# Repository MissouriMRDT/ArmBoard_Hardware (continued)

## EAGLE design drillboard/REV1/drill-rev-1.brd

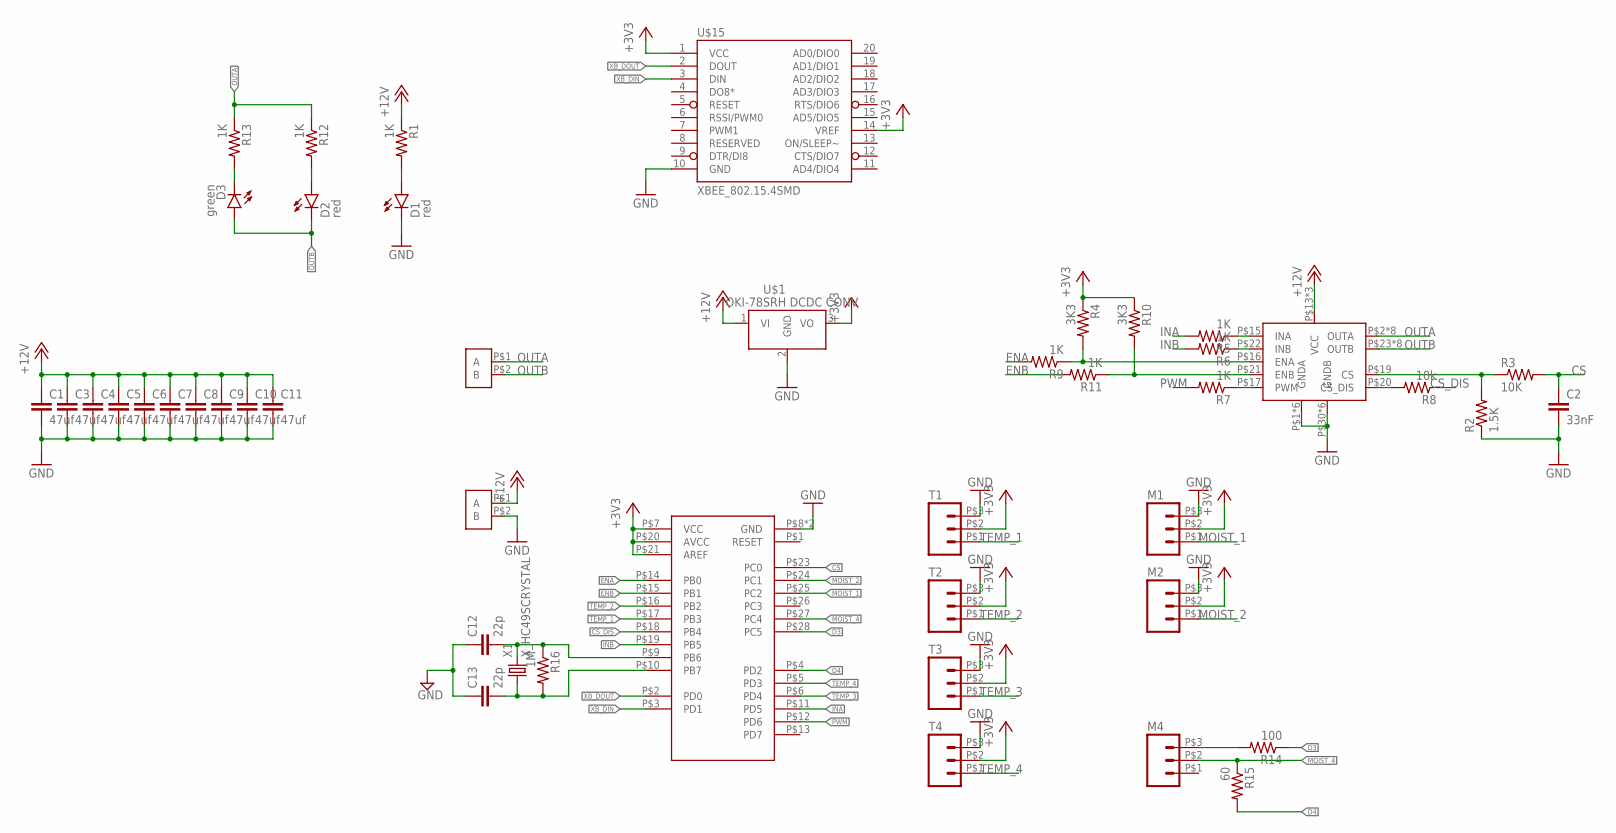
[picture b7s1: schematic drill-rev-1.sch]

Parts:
C1, C3, C4, C5, C6, C7, C8, C9, C10, C11: 47uf; 1210
C2: 33nF; 0603-CAP
C12, C13: 22p; 0603-CAP
D1, D2: red; LED-0603
D3: green; LED-0603
M1, M2, M4: M03VERT; MOLEX0436500328
R1, R5, R6, R7, R9, R11, R12, R13: 1K; 0603-RES
R2: 1.5K; 0603-RES
R3: 10K; 0603-RES
R4, R10: 3K3; 0603-RES
R8: 10k; 0603-RES
R14: 100; 1206
R15: 60; 1206
R16: 1M; 0603-RES
T1, T2, T3, T4: M03VERT; MOLEX0436500328
U$1: Q_OKI-78SR; OKI-78SR_HORIZ
U$3, U$5: TE_2POS-5MM_SCREW_TERM
U$6: VNH5XXX_HBRIDGEVNH5050A; POWERSSO-36_TP
U$13: DIP_SKT_ATMEGA
U$15: XBEE_802.15.4SMD; XBEE_802.15.4_SMD
X1: X_HC49SCRYSTAL; HC-49

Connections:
+3V3: M1.P$2 (2), M2.P$2 (2), R4.1, R10.1, T1.P$2 (2), T2.P$2 (2), T3.P$2 (2), T4.P$2 (2), U$1.3 (VO), U$13.P$7 (VCC), U$13.P$20 (AVCC), U$13.P$21 (AREF), U$15.1 (VCC), U$15.14 (VREF)
+12V: C1.1, C3.1, C4.1, C5.1, C6.1, C7.1, C8.1, C9.1, C10.1, C11.1, R1.1, U$1.1 (VI), U$5.P$1 (A), U$6.P$13 (VCC), U$6.P$24 (VCC), U$6.SLUG1 (VCC)
CS: C2.1, R3.2, U$13.P$23 (PC0)
CS_DIS: R8.1, U$13.P$18 (PB4)
D3: R14.1, U$13.P$28 (PC5)
D4: R15.2, U$13.P$4 (PD2)
ENA: R9.2, U$13.P$14 (PB0)
ENB: R11.2, U$13.P$15 (PB1)
GND: C1.2, C2.2, C3.2, C4.2, C5.2, C6.2, C7.2, C8.2, C9.2, C10.2, C11.2, C12.1, C13.1, D1.C, M1.P$3 (3), M2.P$3 (3), R2.1, T1.P$3 (3), T2.P$3 (3), T3.P$3 (3), T4.P$3 (3), U$1.2 (GND), U$5.P$2 (B), U$6.P$1 (GNDA), U$6.P$3 (GNDA), U$6.P$4 (GNDA), U$6.P$5 (GNDA), U$6.P$6 (GNDA), U$6.P$7 (GNDA), U$6.P$30 (GNDB), U$6.P$31 (GNDB), U$6.P$32 (GNDB), U$6.P$33 (GNDB), U$6.P$34 (GNDB), U$6.P$36 (GNDB), U$13.P$8 (GND), U$13.P$22 (GND), U$15.10 (GND)
INA: R5.2, U$13.P$11 (PD5)
INB: R6.2, U$13.P$19 (PB5)
MOIST_1: M1.P$1 (1), U$13.P$25 (PC2)
MOIST_2: M2.P$1 (1), U$13.P$24 (PC1)
MOIST_4: M4.P$2 (2), R15.1, U$13.P$27 (PC4)
unnamed: M4.P$3 (3), R14.2
unnamed: R4.2, R9.1, U$6.P$16 (ENA)
unnamed: R2.2, R3.1, U$6.P$19 (CS)
unnamed: D1.A, R1.2
unnamed: D2.A, R12.2
unnamed: R10.2, R11.1, U$6.P$21 (ENB)
unnamed: R5.1, U$6.P$15 (INA)
unnamed: R6.1, U$6.P$22 (INB)
unnamed: R7.1, U$6.P$17 (PWM)
unnamed: R8.2, U$6.P$20 (CS_DIS)
unnamed: D3.C, R13.2
OUTA: R12.1, R13.1, U$3.P$1 (A), U$6.P$2 (OUTA), U$6.P$8 (OUTA), U$6.P$9 (OUTA), U$6.P$10 (OUTA), U$6.P$11 (OUTA), U$6.P$12 (OUTA), U$6.P$14 (OUTA), U$6.SLUG2 (OUTA)
OUTB: D2.C, D3.A, U$3.P$2 (B), U$6.P$23 (OUTB), U$6.P$25 (OUTB), U$6.P$26 (OUTB), U$6.P$27 (OUTB), U$6.P$28 (OUTB), U$6.P$29 (OUTB), U$6.P$35 (OUTB), U$6.SLUG3 (OUTB)
PWM: R7.2, U$13.P$12 (PD6)
TEMP_1: T1.P$1 (1), U$13.P$17 (PB3)
TEMP_2: T2.P$1 (1), U$13.P$16 (PB2)
TEMP_3: T3.P$1 (1), U$13.P$6 (PD4)
TEMP_4: T4.P$1 (1), U$13.P$5 (PD3)
XB_DIN: U$13.P$3 (PD1), U$15.3 (DIN)
XB_DOUT: U$13.P$2 (PD0), U$15.2 (DOUT)
XTAL1: C12.2, R16.1, U$13.P$9 (PB6), X1.P$2 (2)
XTAL2: C13.2, R16.2, U$13.P$10 (PB7), X1.P$1 (1)

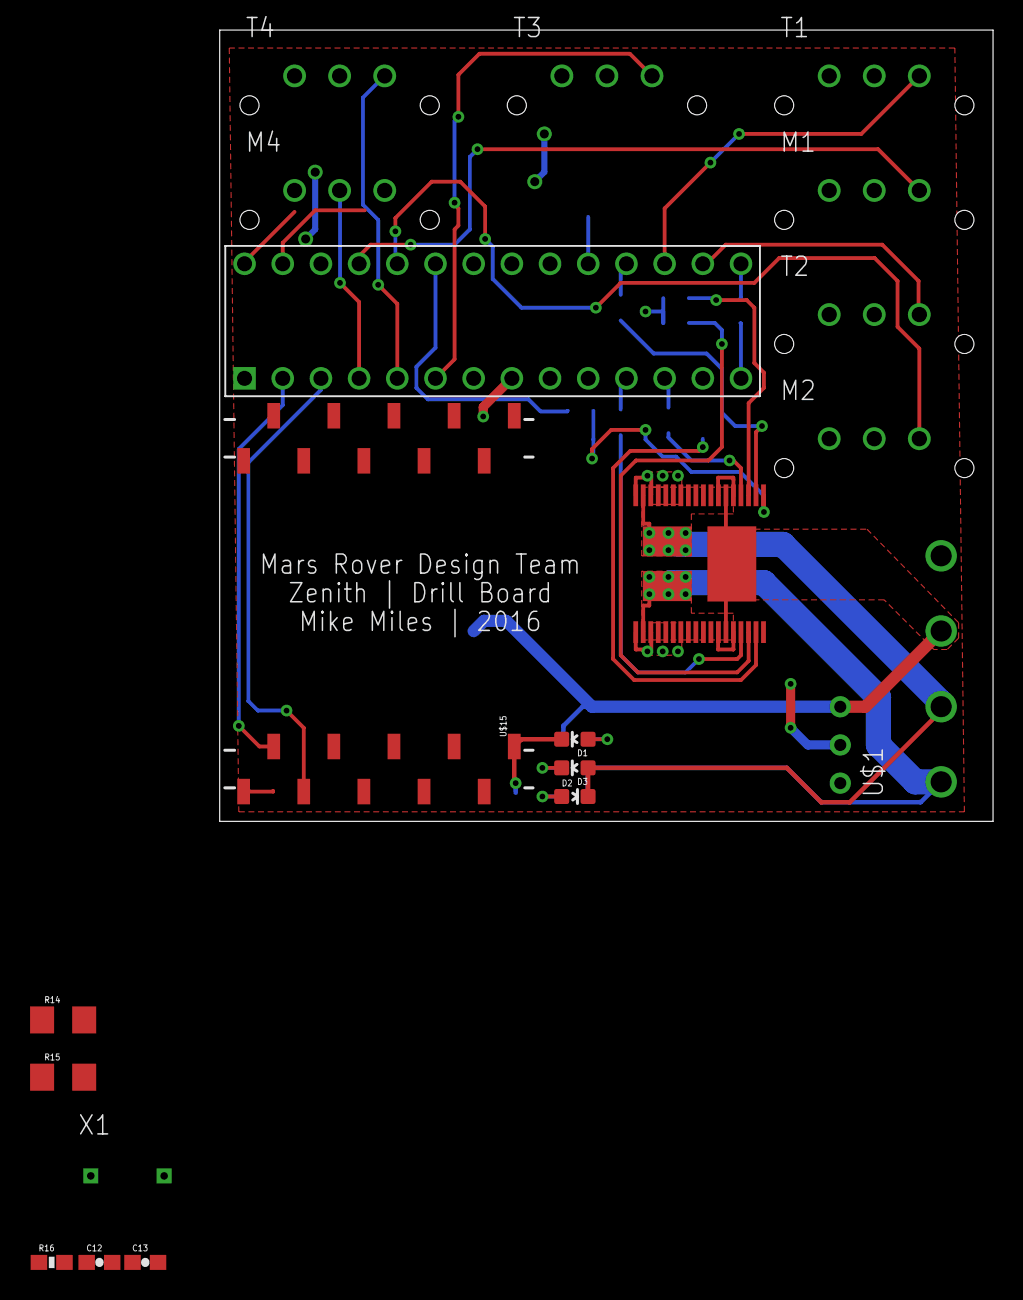
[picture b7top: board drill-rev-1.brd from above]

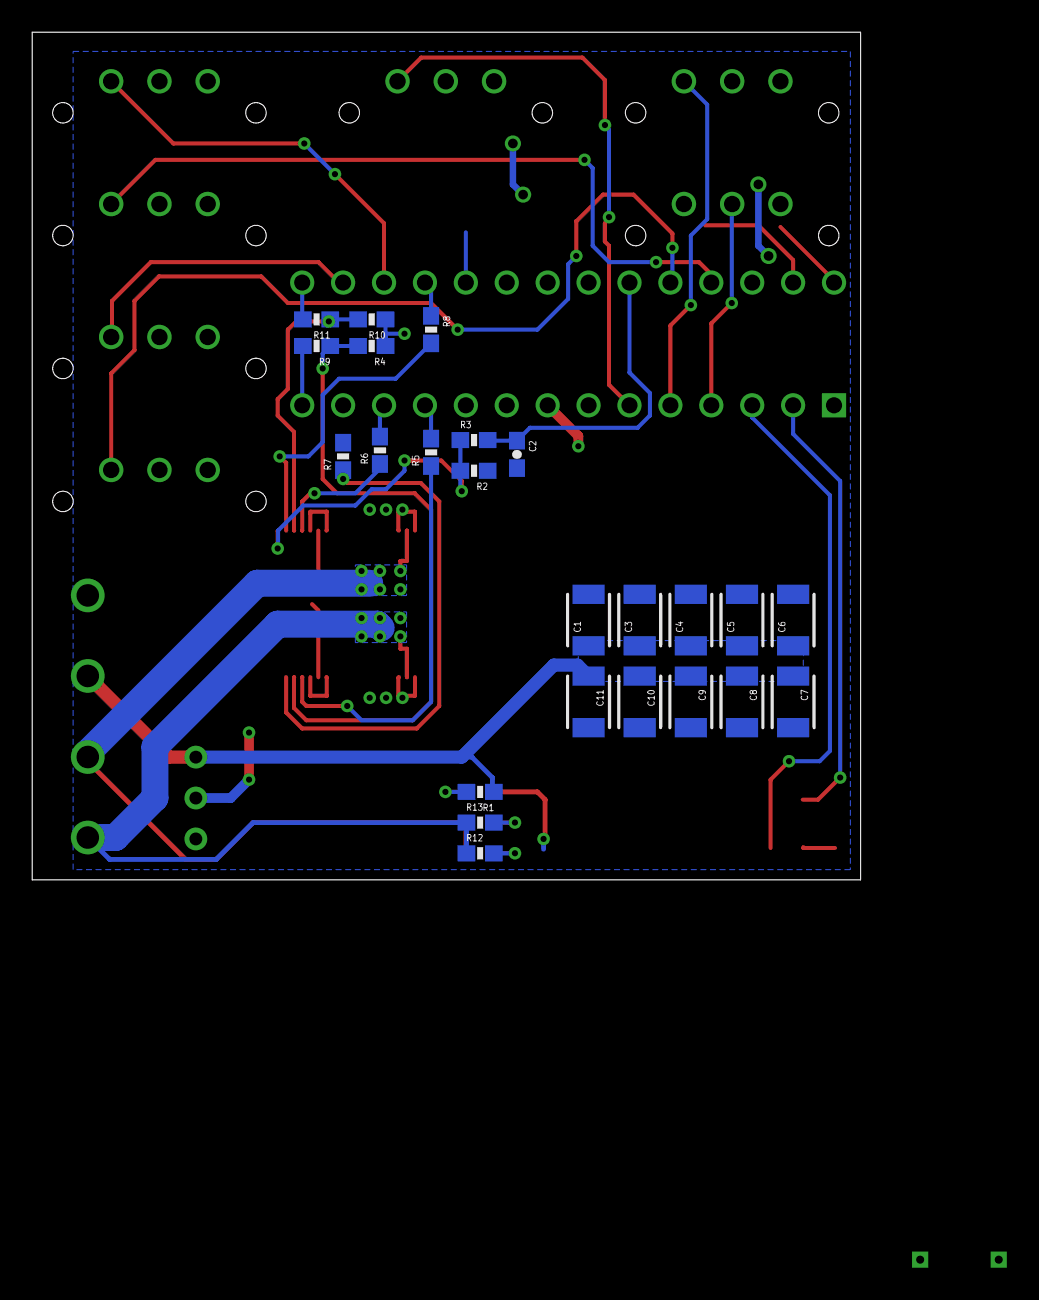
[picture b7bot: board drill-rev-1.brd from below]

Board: 2 copper layers, 51.4 x 52.6 mm, 46 parts (24 on the bottom side), 36 nets.

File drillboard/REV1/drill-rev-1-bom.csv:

"Qty";"Value";"Device";"Package";"Parts";"Description";"";
"1";"1.5K";"RESISTOR0603";"0603-RES";"R2";"Resistor";"";
"1";"10K";"RESISTOR0603";"0603-RES";"R3";"Resistor";"";
"1";"10k";"RESISTOR0603";"0603-RES";"R8";"Resistor";"";
"8";"1K";"RESISTOR0603";"0603-RES";"R1, R5, R6, R7, R9, R11, R12, R13";"Resistor";"";
"1";"33nF";"CAP0603-CAP";"0603-CAP";"C2";"Capacitor";"";
"2";"3K3";"RESISTOR0603";"0603-RES";"R4, R10";"Resistor";"";
"10";"47uf";"CAP1210";"1210";"C1, C3, C4, C5, C6, C7, C8, C9, C10, C11";"Capacitor";"";
"1";"DIP_SKT_ATMEGA";"DIP_SKT_ATMEGA";"DIP_SKT_ATMEGA";"U$13";"";"";
"8";"M03VERT";"M03VERT";"MOLEX0436500328";"M1, M2, M3, M4, T1, T2, T3, T4";"";"";
"1";"Q_OKI-78SR";"Q_OKI-78SR";"OKI-78SR_HORIZ";"U$1";"4.95W DC/DC Converter";"";
"2";"TE_2POS-5MM_SCREW_TERM";"TE_2POS-5MM_SCREW_TERM";"TE_2POS-5MM_SCREW_TERM";"U$3, U$5";"";"";
"1";"VNH5XXX_HBRIDGEVNH5050A";"VNH5XXX_HBRIDGEVNH5050A";"POWERSSO-36_TP";"U$6";"";"";
"1";"XBEE_802.15.4SMD";"XBEE_802.15.4SMD";"XBEE_802.15.4_SMD";"U$15";"";"";
"1";"green";"LED0603";"LED-0603";"D3";"LEDs";"";
"2";"red";"LED0603";"LED-0603";"D1, D2";"LEDs";"";

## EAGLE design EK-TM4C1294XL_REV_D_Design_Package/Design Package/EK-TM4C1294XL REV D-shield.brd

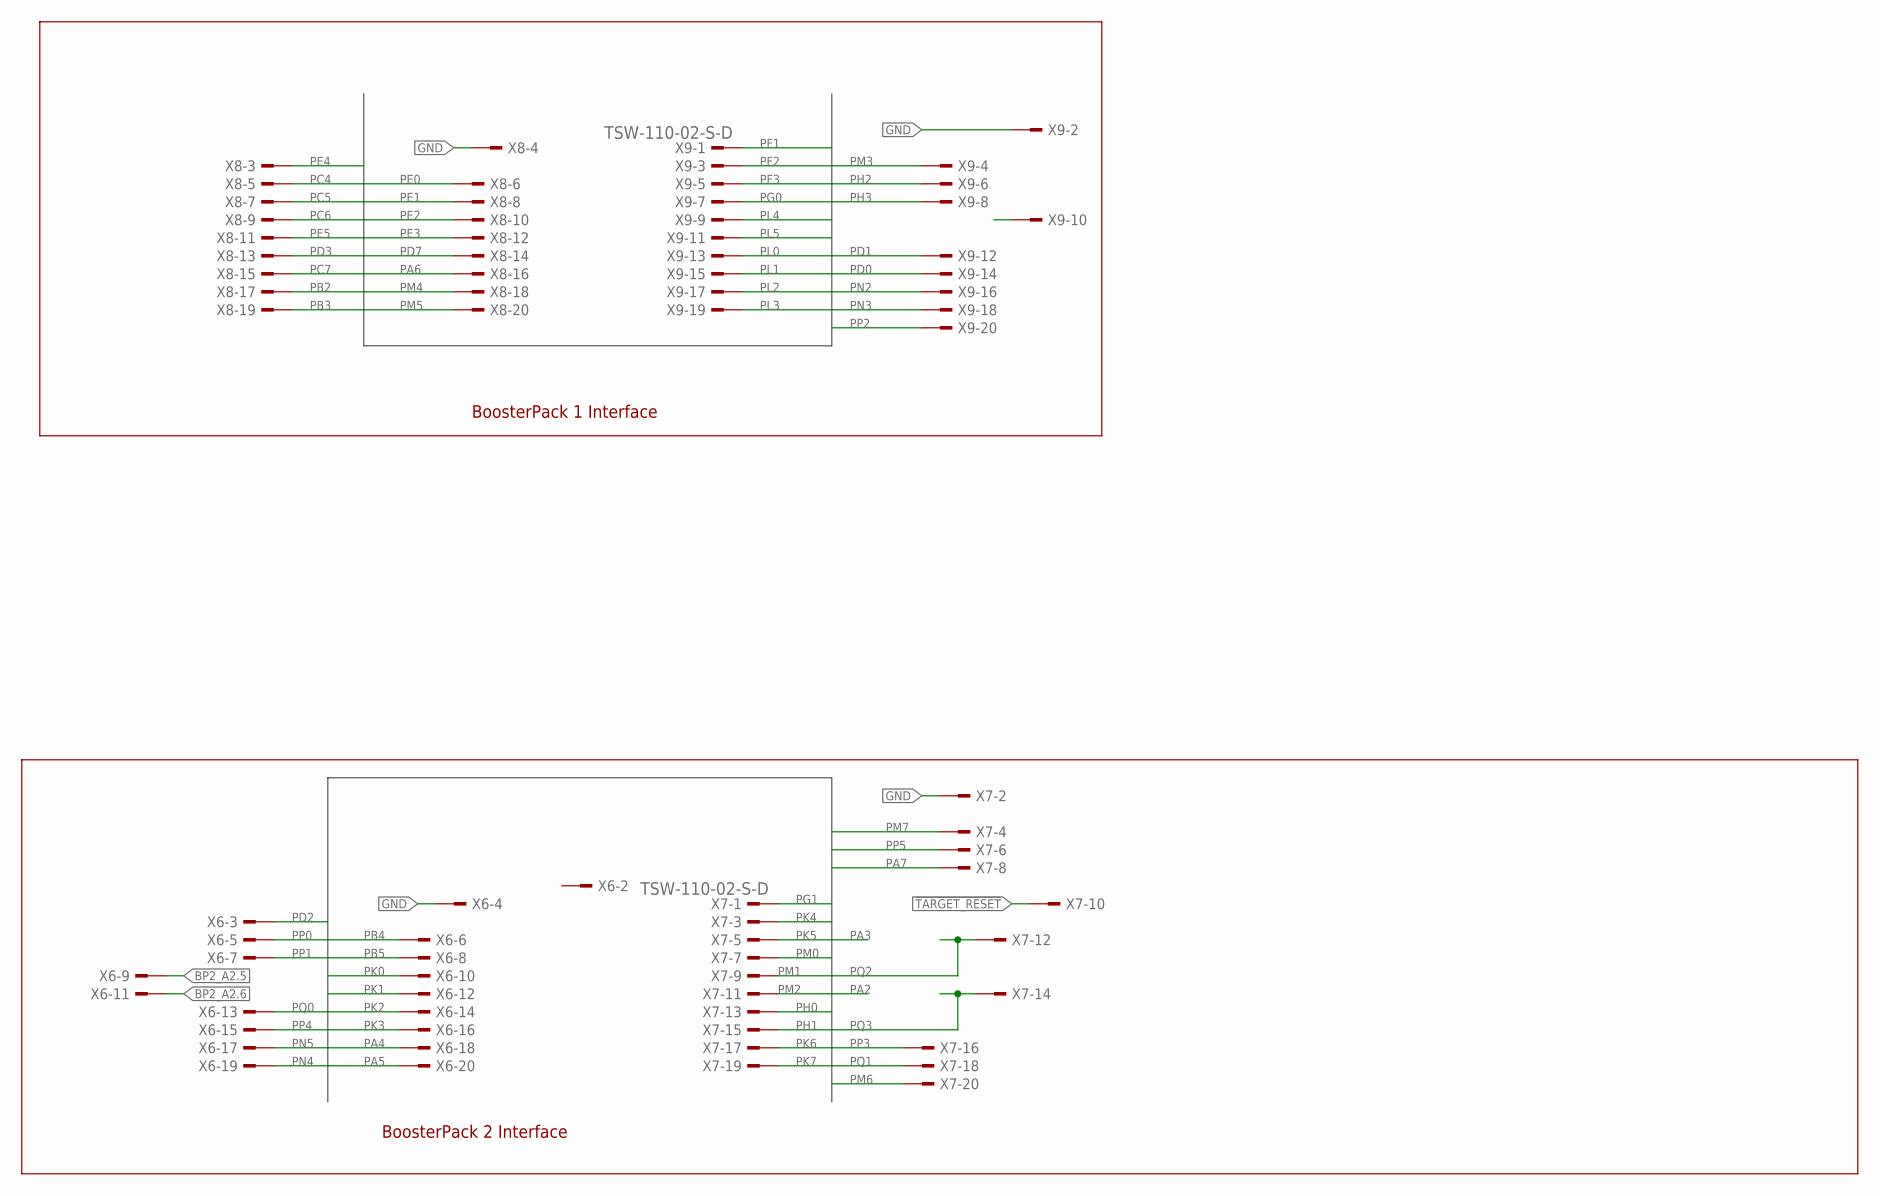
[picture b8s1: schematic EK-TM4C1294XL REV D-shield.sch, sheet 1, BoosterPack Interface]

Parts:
X6, X7, X8, X9: TSW-110-02-S-D

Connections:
!TARGET_RESET: X7.10, X9.10
BP2_A2.5: X6.9
BP2_A2.6: X6.11
GND: X6.4, X7.2, X8.4, X9.2
PA4: X6.18
PA5: X6.20
PA6: X8.16
PA7: X7.8
PB2: X8.17
PB3: X8.19
PB4: X6.6
PB5: X6.8
PC4: X8.5
PC5: X8.7
PC6: X8.9
PC7: X8.15
PD0: X9.14
PD1: X9.12
PD2: X6.3
PD3: X8.13
PD7: X8.14
PE0: X8.6
PE1: X8.8
PE2: X8.10
PE3: X8.12
PE4: X8.3
PE5: X8.11
PF1: X9.1
PF2: X9.3
PF3: X9.5
PG0: X9.7
PG1: X7.1
PH0: X7.13
PH1: X7.15
PH2: X9.6
PH3: X9.8
PK0: X6.10
PK1: X6.12
PK2: X6.14
PK3: X6.16
PK4: X7.3
PK5: X7.5
PK6: X7.17
PK7: X7.19
PL0: X9.13
PL1: X9.15
PL2: X9.17
PL3: X9.19
PL4: X9.9
PL5: X9.11
PM0: X7.7
PM1: X7.9
PM2: X7.11
PM3: X9.4
PM4: X8.18
PM5: X8.20
PM6: X7.20
PM7: X7.4
PN2: X9.16
PN3: X9.18
PN4: X6.19
PN5: X6.17
PP0: X6.5
PP1: X6.7
PP2: X9.20
PP3: X7.16
PP4: X6.15
PP5: X7.6
PQ0: X6.13
PQ1: X7.18
PQ2: X7.12
PQ3: X7.14

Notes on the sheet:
BoosterPack 2 Interface
BoosterPack 1 Interface

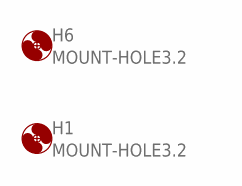
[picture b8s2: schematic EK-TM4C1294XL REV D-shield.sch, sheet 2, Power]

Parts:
H1, H6: MOUNT-HOLE3.2; 3,2

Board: 4 copper layers, 6 parts (4 on the bottom side), 2 nets, no tracks yet.

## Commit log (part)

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2019-11-21 Added Silks, 100% done
2019-11-21 eat a bagel
2019-12-05 Frick me, my B
2019-12-06 Reducing Electrical Leads bitching potential
2019-12-07 Hurt me daddy
2019-12-07 Suck my toes
2020-01-21 Created Step FIle
2020-02-06 3 up, three down, suck my toes
2020-02-26 Generated Gerbs
2020-08-24 Renaming things for documentation
2021-10-01 Init Commit
    Removed old files. Added new project, reference docs,
2021-10-02 Moved everything to a new format. Instead of using global lables I used hierarchical so it would look better. needs to be double checked. check and make sure we dont have any unused schematic files
2021-10-15 Pwms have been routed to Pwm Pins. and I added the laser and solenoid mosfets and connectors
2021-10-16 made the main sch smaller
2021-10-16 moved text
2021-10-16 wire fix
2021-10-16 Pin Assignments
2021-10-16 Updated Numbering and BOM
2021-10-21 Added Schematics
2021-11-08 need to change the mosfet and the other footrpints under it
2021-11-10 Updated Symbols
    Fixed orientation of Led Fets, removed Fets for fault detection indicators to minimize components
2021-11-10 beginning layout, need to double check footprints and create BOM
2021-11-12 layout
2021-11-16 week 2 of layout. andersons fixed and are in correct direction for now. moved VNHs up. plan to put tiva on back of board.
2021-11-16 extended board by 0.5in to height
2021-11-16 components over top of moco VNHs
2021-11-17 yeet
2021-11-17 yeet2
2021-11-17 late night with the boy
2021-11-20 Fixed Oscillators
2021-11-24 Worked on Motor Drivers
    added major tracing of motor drivers
2021-11-24 Power Rails and LEDs
    Routed Power and Power Indicators, starting to route signals
2021-11-27 Routed Major Signals
2021-11-27 All Routing Done
    Ran DRC with all checking options, fixed any errors
2021-12-01 armboard review
2021-12-02 Removed all signal routing
    Whelp it's gonna look better by tonight
2021-12-02 Updated Footprints
2021-12-02 LEDs routed, footprints correctly assigned
2021-12-03 Rerouted all traces
2021-12-03 silk screen rev1
2021-12-04 Replaced Fets
2021-12-08 generated gerbs and step files
2021-12-31 Rescued the Libaries
2021-12-31 removed rescue library dcm file
2022-01-27 Test Commit
    M1 Vref to gnd trace deleted
2022-02-08 project library cleanup - deleted unused and moved them to one folder
2022-02-09 consept pcb
2022-02-11 Rev 2, still needs new mosfet circuit and new solenoid mosfet tthat can handle it
2022-02-12 minor changes
2022-02-12 bad via on 12va fixed
2022-02-12 get rid of 5v led
2022-02-12 visual improvements
2022-02-15 added limit switches to a total of 6
2022-02-16 cleanup
2022-02-22 Started Changes
    Via spacing and density
2022-02-22 Fixed edge cuts
2022-02-22 Made size smaller
2022-02-22 need to change encoder traces, need to add ground resistors to the vnh's and the led trace needs to be redone
2022-02-26 save before runs
2022-02-26 rev 2 finishing passes
2022-03-03 minor changes, changed the vnh traces
2022-03-05 more changes, realignment of alot of stuff
2022-03-07 moved the andersons
2022-03-07 moved traces
2022-03-08 trace cleanup
2022-03-09 Board Review
2022-03-10 final
2022-03-12 updated BOM
2022-03-15 gerbs added and zipped
2022-03-15 final gerbs
2022-03-16 added names and labeling
2022-04-06 Generated step file
2022-05-07 rev 2.1 updated with new pwm pin from PM2 to Motor1 PWM1 instead of PH3
2022-09-10 Initial design of h-bridge prototype
2022-09-14 Deleted unnecessary autosave file
2022-09-14 The whole gosh dang schematic
2022-09-14 Actually Saved this time
2022-09-19 PDR changes to top h-bridge
2022-09-19 Flipped input and output tags on limit switches, encoders, and laser
2022-09-20 PDR Changes to H-Bridge and Layout
2022-09-20 The Anderson Silkscreens were being annoying so i got rid of them
2022-09-20 Picked a diode for the h-bridge itll work probably idk im tired
2022-10-12 Initial PCB Layout with Revised H-Bridges
2022-10-12 Created extra laser, assigned distinct labels for each h-bridge, updated footprint assignment, updated PCB layout
2022-10-17 Optimizing layout spacing, added silkscreen annotations
2022-10-20 Cleaned up some of the ground plane gaps, various minor changes
2022-10-29 Rearranged Stuff so the ground plane flows nicer
2022-10-31 Added Malacki signature
2022-11-12 Added Inverters to H-Bridges, started Teensy Schematic
2022-11-16 Assigned Teensy pins and added RJ45 port
2022-11-16 Started layout
2022-11-17 Connected inverters
2022-11-17 Changed h-bridge capacitor values
2022-11-17 Cleaned up traces. Reduced overall circuit board footprint
2022-12-21 Enlarged 12V Plane, reran traces for ground continuity
2022-12-23 Started rearranging layout for horizontal teensy
2022-12-29 Board Shrink + Rerout + Pin Reassignment
2022-12-29 Added Ezekiel Allen signature
2023-02-09 Added 6 limit switches
2023-02-09 Added Zeke Signature
2023-03-13 Add buttons and 16:4 priority encoder
2023-03-13 Completed schematic
    Combined laser toggles to save pin space on Teensy. Adjusted buttons from SPDT to SPST with pull-up resistors, to match standard.
2023-03-16 Started routing traces
2023-03-17 More trace work
2023-03-21 Post board review changes
2023-03-21 generated gerbs and cleaned up files
2023-04-11 Fixed incorrect capacitor value
2023-04-12 Added 6 encoders ands 10 limit switches
2023-04-18 Added buttons and connectors for vesc
2023-04-19 Added direction switch and connectors
2023-04-19 Added flags to teensy
2023-04-19 updated teensy to include encoder and limit switches flags
2023-04-20 fixed flags and started PCB
2023-04-20 organized components
2023-04-21 started powerline
2023-04-21 started doing traces
2023-04-21 worked on fixing the board for a bit
2023-04-22 fixed placement and redid board
2023-04-22 Fixed labeling again
2023-05-06 Made STEP file
2023-09-24 Ready for schematic reviews (not)
2023-09-24 Post schematic review
2023-09-28 Changed Anderson to V+ Log instead of V+ Act
2023-10-15 layout spaced components
2023-10-16 some layout review changes
2023-10-31 layout review 2
2023-11-01 final layout for orders
2023-11-05 fourth layout review fixes
2023-11-13 gerbs generated
2024-03-21 Started on ArmBoardRev2
    Laid out general components
2024-03-22 Added RJ45 port and buttons
2024-03-22 Fixed LED
2024-03-22 Finished teensy
2024-03-23 Organized Schematic Layout
    I added changes such as moving things around, separating circuits with lines, and creating titles for each circuit to make it easier to read
2024-03-30 Brady's board rev 3/29
2024-03-30 Updated cap values on oki circuits
2024-04-05 Finishes schematic and applied footprints
2024-04-06 Creation of VNH Rev 2 Board
    Creation of VNH Rev 2 Board created by Sean Duda
2024-04-06 Completed Footprint Assignment
    Completed Footprint Assignment
2024-04-06 Finished andersons
2024-04-06 Placed Components and Made Power Planes
    Placed Components for trace routing, and made power planes for motors and 12V
2024-04-06 Buttons finished
2024-04-07 Teensy traces
2024-04-07 Edited power planes for VNH and routed traces
    Routed signal traces and edited power planes for VNH chip to fit 12V pads
2024-04-08 Layout finished before review
    Added 3v3 and 5V lines
    Need vias for planes
2024-04-08 Reworked Traces to match Arm Board size restraints
    Reworked traces and power planes to meet size and power requirements for the VNH chip, and the size calculations for the new Arm Board Mount
2024-04-08 Fixed missing traces
2024-04-09 Ran traces for ICs
    Ran traces for ICs and connectors to finish the routing on Arm. (Vias needed)
2024-04-09 Placed Vias for 12V plane and reworked traces
    Placed vias for 12V and reworked traces by giving more space from pads on ICs
2024-04-09 Fixed some things on review
2024-04-09 Fixed more things from review notes
    -SW10 3V3 trace routing
    -Fixed 12V trace on solenoid
    -Moved bottom right moco to give room to mounting hole
2024-04-09 Fixed M+/M-
    -Still need to fix capacitor bank locations
2024-04-09 Routed traces for switches and limit switches
    Routed traces for switches, buttons, limit switches, and binary encoders
2024-04-09 Routed traces and tweaked power planes
    Routed traces for IO expanders and tweaked 12V power planes
2024-04-10 Fixed labels on IO extenders
2024-04-10 Removed 12V Power plane, and traces
    Removed 12V power plane, and traces. Moved Anderson's for easier 12V plane connection
2024-04-10 layed out most of moco circuits
2024-04-11 Added Will Face, Adjusted Vias, 12V plane extend to right andy
2024-04-11 placed all components, some routing done; should be mostly connect the dots at this point
2024-04-11 Fixed
    -12V plane cutting off ground
    -sharp corners on traces
    -Changed button labels
2024-04-12 Fix 12V and motor output plane overlap
2024-04-12 finished layout
2024-04-13 Fixed ground plane to through hole caps
2024-04-13 Fixed 5V traces from oki to SLs
2024-09-23 Added KiCAD files
2024-09-27 Placed Components
    Boom
2024-09-29 Encoder/Decoders
2024-10-02 Added teensy labels
2024-10-04 Edits made in Moco SIgnals
2024-10-05 Changes made
    Deleted extra wire
2024-10-05 removed extra files
2024-10-10 psuh
2024-10-16 Grounded standby on CAN transceiver
2024-10-18 update footprints
2024-10-21 Edit on PCB and footprints
    Please pop up this time
2024-10-21 Fixed Footprint assignments
2024-10-22 Layout updated
2024-10-23 schematic update
2024-10-24 Layout editted
2024-10-24 Referred to past layouts
2024-10-27 Revert "Made Gerbs"
    This reverts commit e8fd2e3e654022122d892e8da1e72b2455c4286f.
2024-10-27 Revert "gerbs"
    This reverts commit 07dacdaaa2a46f5aa43cc62f0396f5798a40864e.
2024-10-28 Grouped switches done
    Still doing for signals and encoders
2024-10-29 Layout arrangement done, traces connected on OKIs
    Not finalized but will get back to change the arrangement of SL if needed
2024-11-01 Adjusted mosfet connections, previously was wrong
2024-11-02 Progress to get board dimensions
2024-11-02 Passed DRC and added diff pair
2024-11-05 Removed blue traces to make new layout arrangement
2024-11-07 Removed red traces to rearrange components
2024-11-07 Removed traces
2024-11-11 Jesse bitchin
2024-11-11 changes after board grilling
2024-11-12 Double check to see changes were fully pushed into Github
2024-11-18 LEDs compacted more to OKIs, SL connection adjusted (might need to redo), IO expanders position changed
2025-09-06 Inital commit
2025-09-12 Added workflow
2025-10-03 Power Sheet Started :3
2025-10-05 CAN Sheet Started w/ Hierarchical Labels :D
2025-10-06 Added Buttons/Ethernet
    Added 14 buttons a direction switch and a ethernet port
2025-10-06 Fixing push ?
2025-10-06 Revert "Added Buttons/Ethernet"
    This reverts commit 9980516216efd01912de7bddb560febaf0714407.
2025-10-06 Fix gitignore
2025-10-07 Buttons UwU
    Placed 14 buttons and a direction switch.
2025-10-07 Changing CRX and CTX Round 2 :((
2025-10-07 Added Servos
    Added servo molexs
2025-10-10 Added root pins
    Root beer
2025-10-10 Final 1
2025-10-14 Fixed ground
    fixed ground in MCU and added no connect flags.
2025-10-22 Schematic review changes part 2 the electric boogaloo
    finished fixing schematic. Made better names for heiracal pins. Made LED ressistors standard values.
2025-10-23 Prototype Layout
    Made an initial Layout to be edited and changed uwu
2025-10-29 Added Labels/ fixed edge
    Added labels to molexs and fixed board cut out
2025-10-30 Began Traces and shrunk board complete redesign
    Complete3ly redid the board to be smaller and make traces
2025-10-31 signal matchinfg
2025-10-31 Traces done needs to be lengthened slightly
    traces should be good but board needs to be a tad bit longer for labels and possible components in the future
2025-11-10 Minor fixes
2025-11-11 Fixed Labels, Molex, Added silkscreen
2025-11-13 Labeled Laser LED
    Labeles yippie
2025-11-16 Fix reverse voltage protection circuit
2025-11-17 Fix DRC Errors
2025-11-17 Fixed silkscreen
2025-11-17 Fixed power plane
2025-11-17 Shift around diode a lil bit
2026-03-18 Rev 2 start
    Fixed schematic for Rev 2, needs layout changes see sharepoint
2026-03-19 Changed silkscreens and positions of components for Rev2 + Schematic
2026-03-20 SilkScreen
    Added Silkscreen
2026-03-20 Add soldermask remove and plated holes
